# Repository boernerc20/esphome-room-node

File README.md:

# Jarvis Room Node

An ESP32-S3 voice assistant and room sensor for [Home Assistant](https://www.home-assistant.io/),
built on [ESPHome](https://esphome.io/). Wake word ("hey jarvis") on the device, temperature
and humidity, e-ink display, LED status ring.

**Status:** breadboard works end to end. Next: rev A PCB in KiCad.

## Repo

| Path | What |
|---|---|
| [`room-node.yaml`](room-node.yaml) | ESPHome firmware (breadboard pins) |
| [`docs/breadboard.md`](docs/breadboard.md) | Breadboard wiring |
| [`docs/pcb/pinout.md`](docs/pcb/pinout.md) | Rev A PCB pinout |
| [`docs/pcb/schematic.md`](docs/pcb/schematic.md) | Rev A schematic, sheet by sheet — draw from this |
| [`docs/pcb/layout.md`](docs/pcb/layout.md) | Rev A board (placed + routed), assembly and bring-up |
| [`docs/enclosure.md`](docs/enclosure.md) | Enclosure notes |
| `kicad/room-node/` | KiCad project |
| `reports/bom/rev-a-bom-lcsc.csv` | Rev A BOM with LCSC numbers |
| `models/` | Wake word model |

## Flash

1. Copy `secrets.yaml.example` to `secrets.yaml` and fill it in. Git ignores it.
2. `esphome run room-node.yaml` — USB the first time, then OTA (192.168.1.50).
3. Home Assistant finds the node. Assign an Assist pipeline under **Settings → Voice assistants**.

Built by [Chris Boerner](https://boernerc20.me).

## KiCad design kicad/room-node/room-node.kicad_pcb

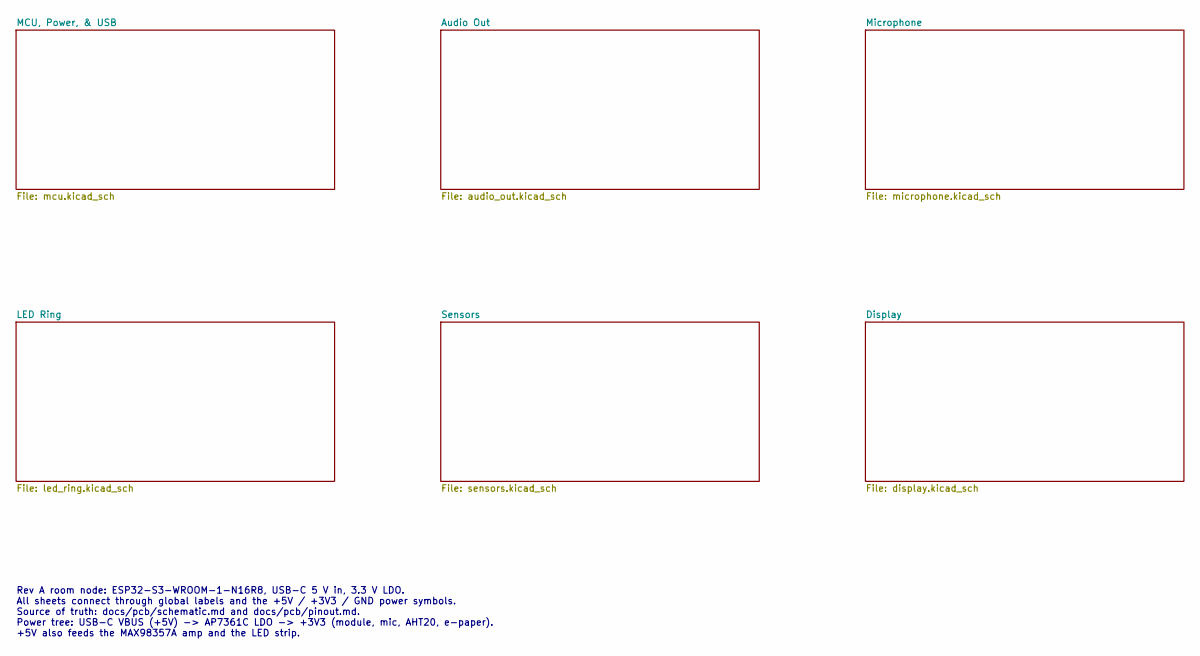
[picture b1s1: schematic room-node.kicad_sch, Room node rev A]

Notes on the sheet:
Rev A room node: ESP32-S3-WROOM-1-N16R8, USB-C 5 V in, 3.3 V LDO. All sheets connect through global labels and the +5V / +3V3 / GND power symbols. Source of truth: docs/pcb/schematic.md and docs/pcb/pinout.md. Power tree: USB-C VBUS (+5V) -> AP7361C LDO -> +3V3 (module, mic, AHT20, e-paper). +5V al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

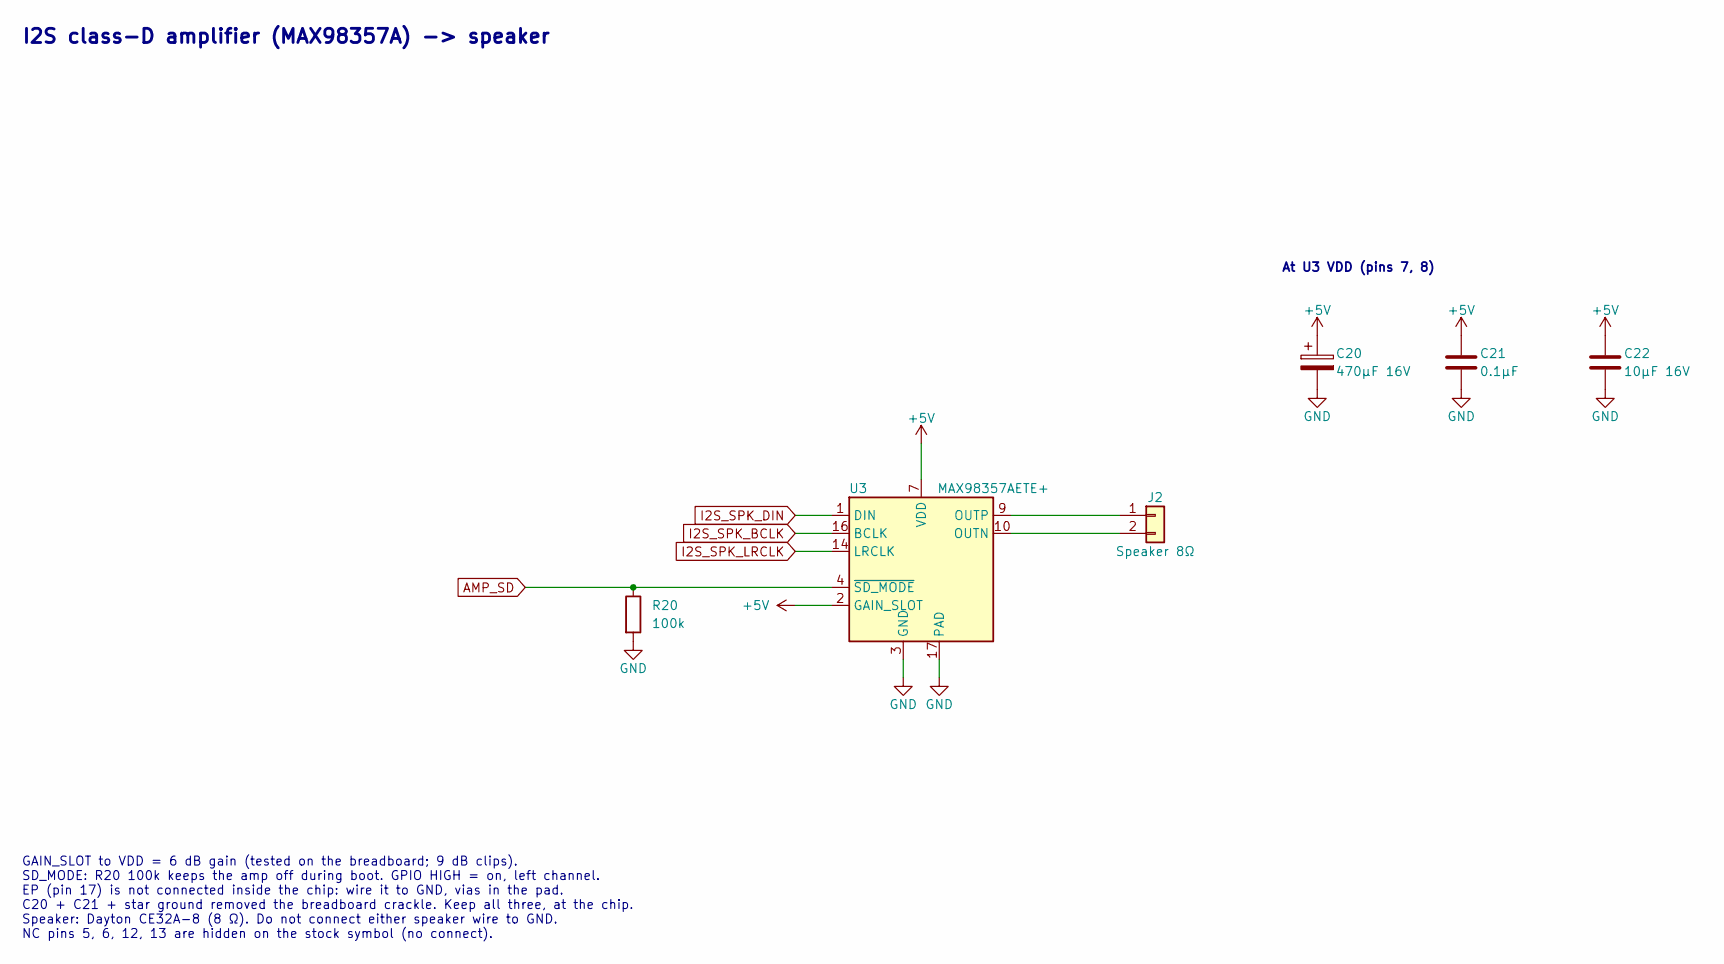
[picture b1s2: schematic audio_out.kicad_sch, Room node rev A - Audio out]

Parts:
C20: 470µF 16V; CP_Radial_D8.0mm_P3.50mm; MPN SamYoung NXB16V470M8*11.5; LCSC C346937
C21: 0.1µF; C_0603_1608Metric; LCSC C14663
C22: 10µF 16V; C_0805_2012Metric; LCSC C15850
J2: Speaker 8Ω; JST_PH_B2B-PH-SM4-TB_1x02-1MP_P2.00mm_Vertical; MPN JST B2B-PH-SM4-TB(LF)(SN); LCSC C160352
R20: 100k; R_0603_1608Metric; LCSC C25803
U3: MAX98357AETE+; TQFN-16-1EP_3x3mm_P0.5mm_EP1.23x1.23mm; MPN Analog Devices MAX98357AETE+; LCSC TBD

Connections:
+5V: C20.1, C21.1, C22.1, U3.2 (GAIN_SLOT), U3.7 (VDD), U3.8 (VDD); also elsewhere on the board
AMP_SD: R20.1, U3.4 (~SD_MODE); also elsewhere on the board
GND: C20.2, C21.2, C22.2, R20.2, U3.3 (GND), U3.11 (GND), U3.15 (GND), U3.17 (PAD); also elsewhere on the board
I2S_SPK_BCLK: U3.16 (BCLK); also elsewhere on the board
I2S_SPK_DIN: U3.1 (DIN); also elsewhere on the board
I2S_SPK_LRCLK: U3.14 (LRCLK); also elsewhere on the board
unnamed: J2.1, U3.9 (OUTP)
unnamed: J2.2, U3.10 (OUTN)

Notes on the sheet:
I2S class-D amplifier (MAX98357A) -> speaker
At U3 VDD (pins 7, 8)
GAIN_SLOT to VDD = 6 dB gain (tested on the breadboard; 9 dB clips). SD_MODE: R20 100k keeps the amp off during boot. GPIO HIGH = on, left channel. EP (pin 17) is not connected inside the chip: wire it to GND, vias in the pad. C20 + C21 + star ground removed the breadboard crackle. Keep all three, 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

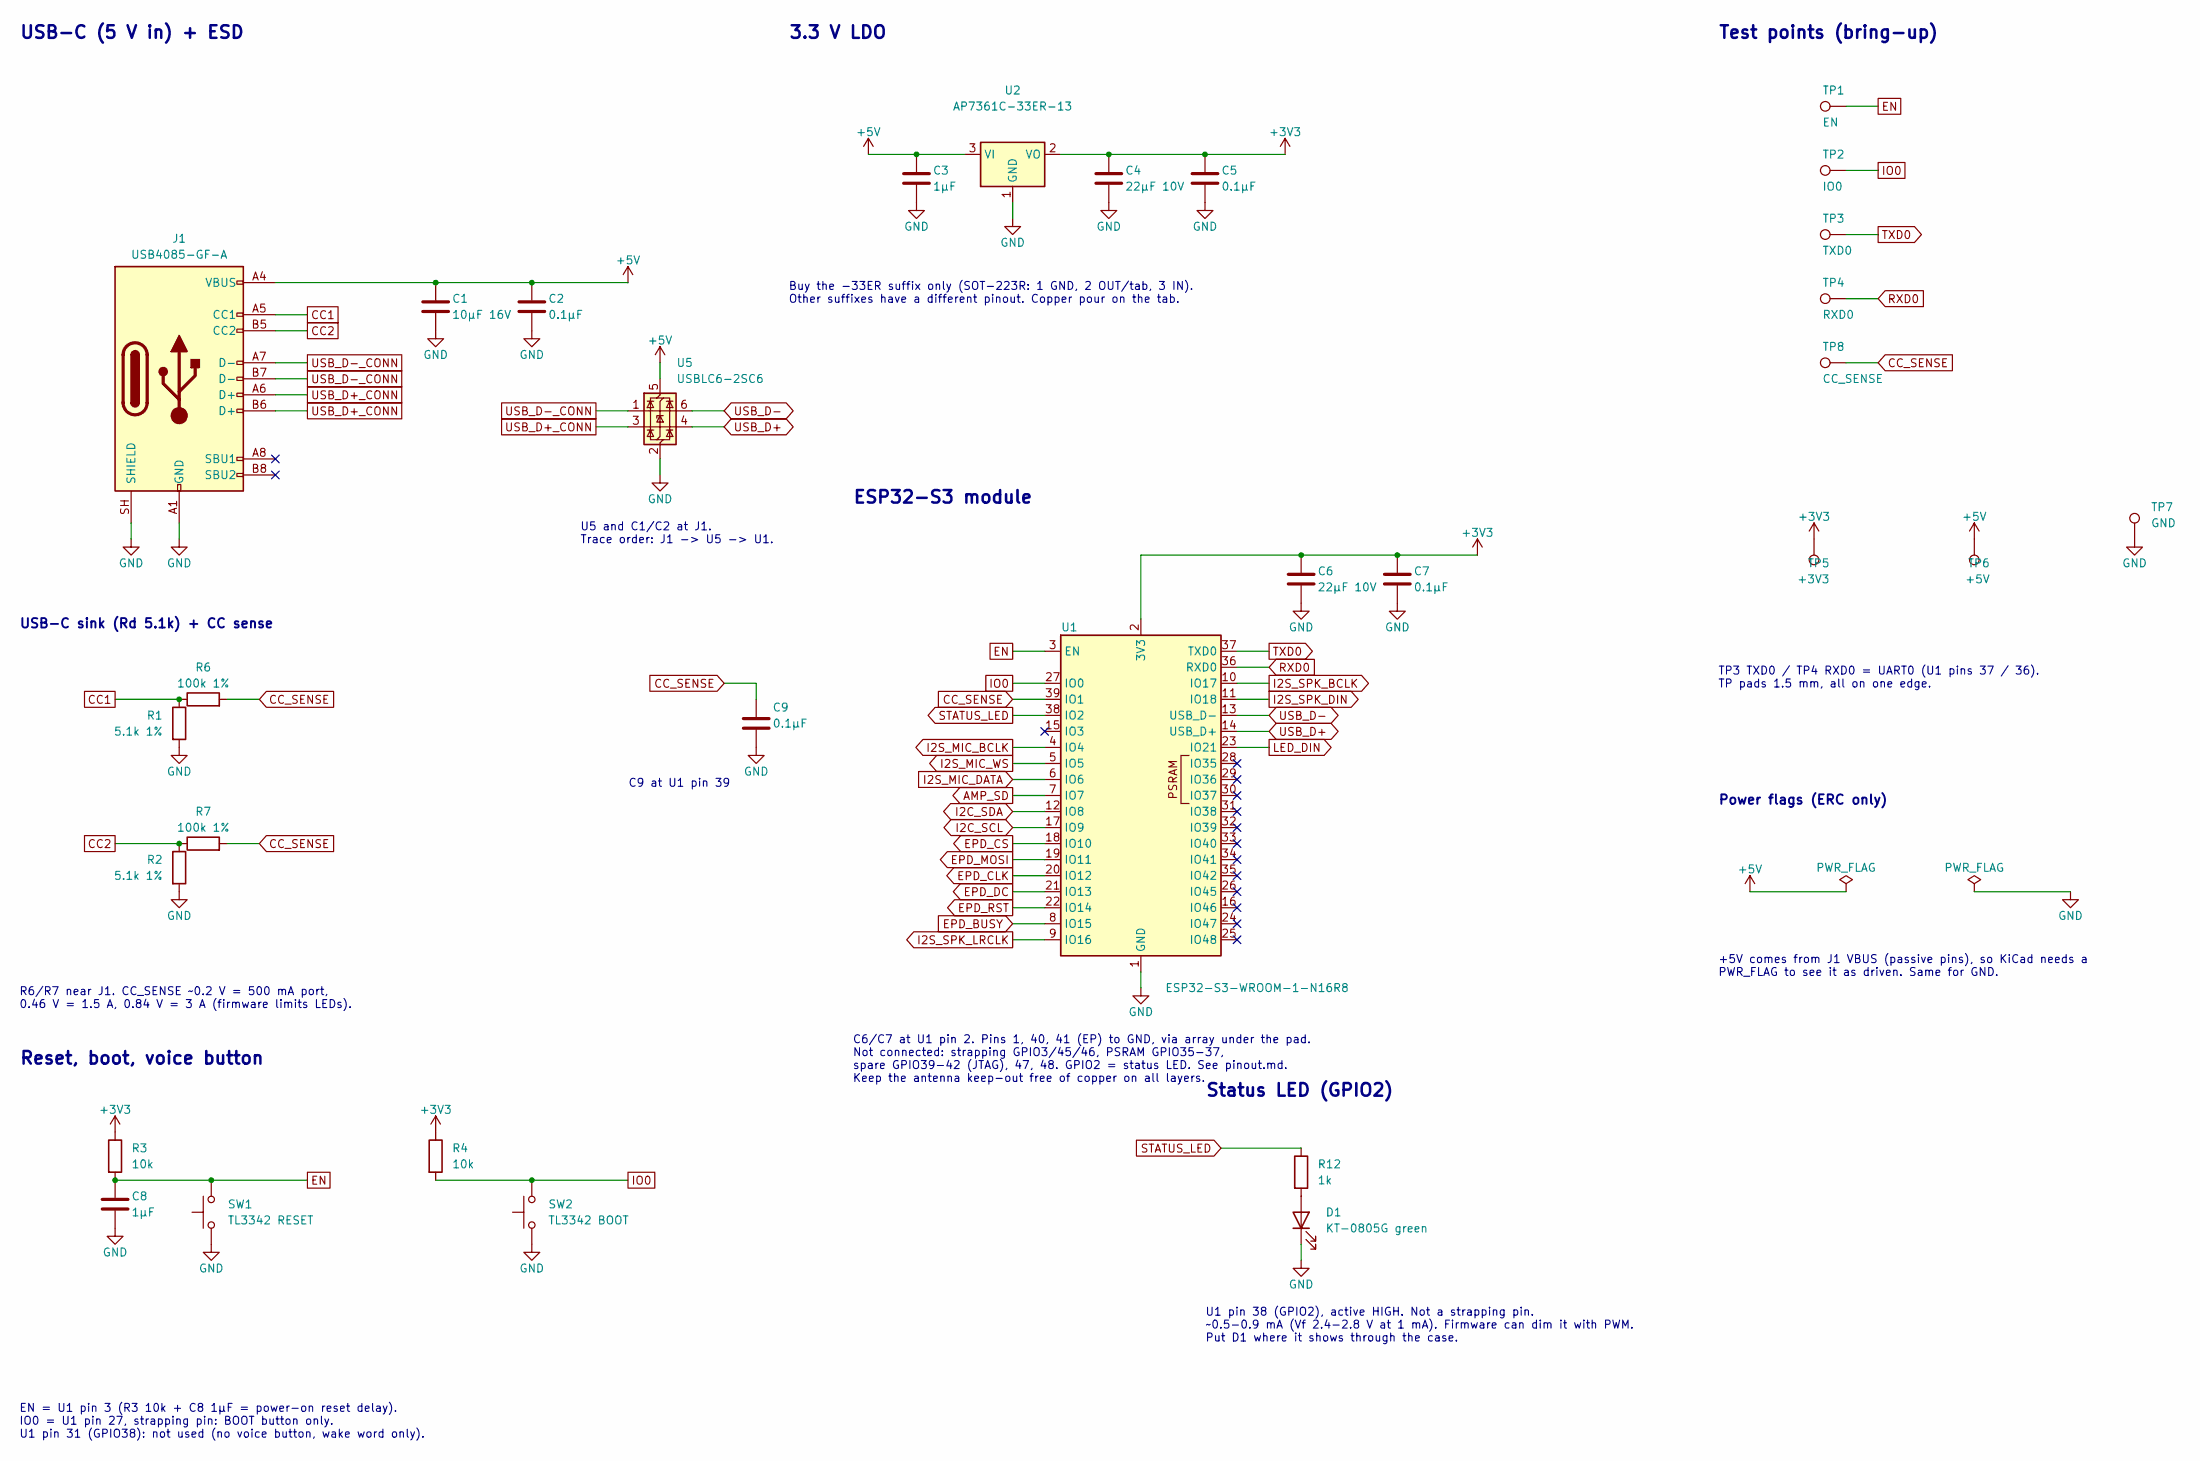
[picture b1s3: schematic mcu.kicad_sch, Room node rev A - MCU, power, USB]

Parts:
C1: 10µF 16V; C_0805_2012Metric; LCSC C15850
C2, C5, C7, C9: 0.1µF; C_0603_1608Metric; LCSC C14663
C3, C8: 1µF; C_0603_1608Metric; LCSC C15849
C4, C6: 22µF 10V; C_0805_2012Metric; LCSC C45783
D1: KT-0805G green; LED_0805_2012Metric; MPN KT-0805G; LCSC C2297
J1: USB4085-GF-A; USB_C_Receptacle_GCT_USB4085; MPN GCT USB4085-GF-A; LCSC TBD
R1, R2: 5.1k 1%; R_0603_1608Metric; LCSC C23186
R3, R4: 10k; R_0603_1608Metric; LCSC C25804
R6, R7: 100k 1%; R_0603_1608Metric; LCSC C25803
R12: 1k; R_0603_1608Metric; LCSC C21190
SW1: TL3342 RESET; SW_SPST_TL3342; MPN E-Switch TL3342F160QG; LCSC TBD
SW2: TL3342 BOOT; SW_SPST_TL3342; MPN E-Switch TL3342F160QG; LCSC TBD
TP1: EN; TestPoint_Pad_D1.5mm
TP2: IO0; TestPoint_Pad_D1.5mm
TP3: TXD0; TestPoint_Pad_D1.5mm
TP4: RXD0; TestPoint_Pad_D1.5mm
TP5: +3V3; TestPoint_Pad_D1.5mm
TP6: +5V; TestPoint_Pad_D1.5mm
TP7: GND; TestPoint_Pad_D1.5mm
TP8: CC_SENSE; TestPoint_Pad_D1.5mm
U1: ESP32-S3-WROOM-1-N16R8; ESP32-S3-WROOM-1; MPN Espressif ESP32-S3-WROOM-1-N16R8; LCSC TBD
U2: AP7361C-33ER-13; SOT-223-3_TabPin2; MPN Diodes AP7361C-33ER-13; LCSC TBD
U5: USBLC6-2SC6; SOT-23-6; MPN ST USBLC6-2SC6; LCSC TBD

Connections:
+3V3: C4.1, C5.1, C6.1, C7.1, R3.1, R4.1, TP5.1, U1.2 (3V3), U2.2 (VO); also elsewhere on the board
+5V: C1.1, C2.1, C3.1, J1.A4 (VBUS), J1.A9 (VBUS), J1.B4 (VBUS), J1.B9 (VBUS), TP6.1, U2.3 (VI), U5.5 (VBUS); also elsewhere on the board
AMP_SD: U1.7 (IO7); also elsewhere on the board
CC1: J1.A5 (CC1), R1.1, R6.1
CC2: J1.B5 (CC2), R2.1, R7.1
CC_SENSE: C9.1, R6.2, R7.2, TP8.1, U1.39 (IO1)
EN: C8.1, R3.2, SW1.2, TP1.1, U1.3 (EN)
EPD_BUSY: U1.8 (IO15); also elsewhere on the board
EPD_CLK: U1.20 (IO12); also elsewhere on the board
EPD_CS: U1.18 (IO10); also elsewhere on the board
EPD_DC: U1.21 (IO13); also elsewhere on the board
EPD_MOSI: U1.19 (IO11); also elsewhere on the board
EPD_RST: U1.22 (IO14); also elsewhere on the board
GND: C1.2, C2.2, C3.2, C4.2, C5.2, C6.2, C7.2, C8.2, C9.2, D1.1 (K), J1.A1 (GND), J1.A12 (GND), J1.B1 (GND), J1.B12 (GND), J1.SH (SHIELD), R1.2, R2.2, SW1.1, SW2.1, TP7.1, U1.1 (GND), U1.40 (GND), U1.41 (GND), U2.1 (GND), U5.2 (GND); also elsewhere on the board
I2C_SCL: U1.17 (IO9); also elsewhere on the board
I2C_SDA: U1.12 (IO8); also elsewhere on the board
I2S_MIC_BCLK: U1.4 (IO4); also elsewhere on the board
I2S_MIC_DATA: U1.6 (IO6); also elsewhere on the board
I2S_MIC_WS: U1.5 (IO5); also elsewhere on the board
I2S_SPK_BCLK: U1.10 (IO17); also elsewhere on the board
I2S_SPK_DIN: U1.11 (IO18); also elsewhere on the board
I2S_SPK_LRCLK: U1.9 (IO16); also elsewhere on the board
IO0: R4.2, SW2.2, TP2.1, U1.27 (IO0)
LED_DIN: U1.23 (IO21); also elsewhere on the board
unnamed: D1.2 (A), R12.2
RXD0: TP4.1, U1.36 (RXD0)
STATUS_LED: R12.1, U1.38 (IO2)
TXD0: TP3.1, U1.37 (TXD0)
USB_D+: U1.14 (USB_D+), U5.4 (I/O2)
USB_D+_CONN: J1.A6 (D+), J1.B6 (D+), U5.3 (I/O2)
USB_D-: U1.13 (USB_D-), U5.6 (I/O1)
USB_D-_CONN: J1.A7 (D-), J1.B7 (D-), U5.1 (I/O1)

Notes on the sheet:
USB-C (5 V in) + ESD
U5 and C1/C2 at J1. Trace order: J1 -> U5 -> U1.
USB-C sink (Rd 5.1k) + CC sense
R6/R7 near J1. CC_SENSE ~0.2 V = 500 mA port, 0.46 V = 1.5 A, 0.84 V = 3 A (firmware limits LEDs).
3.3 V LDO
Buy the -33ER suffix only (SOT-223R: 1 GND, 2 OUT/tab, 3 IN). Other suffixes have a different pinout. Copper pour on the tab.
ESP32-S3 module
C6/C7 at U1 pin 2. Pins 1, 40, 41 (EP) to GND, via array under the pad. Not connected: strapping GPIO3/45/46, PSRAM GPIO35-37, spare GPIO39-42 (JTAG), 47, 48. GPIO2 = status LED. See pinout.md. Keep the antenna keep-out free of copper on all layers.
C9 at U1 pin 39
Reset, boot, voice button
EN = U1 pin 3 (R3 10k + C8 1µF = power-on reset delay). IO0 = U1 pin 27, strapping pin: BOOT button only. U1 pin 31 (GPIO38): not used (no voice button, wake word only).
Test points (bring-up)
TP3 TXD0 / TP4 RXD0 = UART0 (U1 pins 37 / 36). TP pads 1.5 mm, all on one edge.
Power flags (ERC only)
+5V comes from J1 VBUS (passive pins), so KiCad needs a PWR_FLAG to see it as driven. Same for GND.
Status LED (GPIO2)
U1 pin 38 (GPIO2), active HIGH. Not a strapping pin. ~0.5-0.9 mA (Vf 2.4-2.8 V at 1 mA). Firmware can dim it with PWM. Put D1 where it shows through the case.

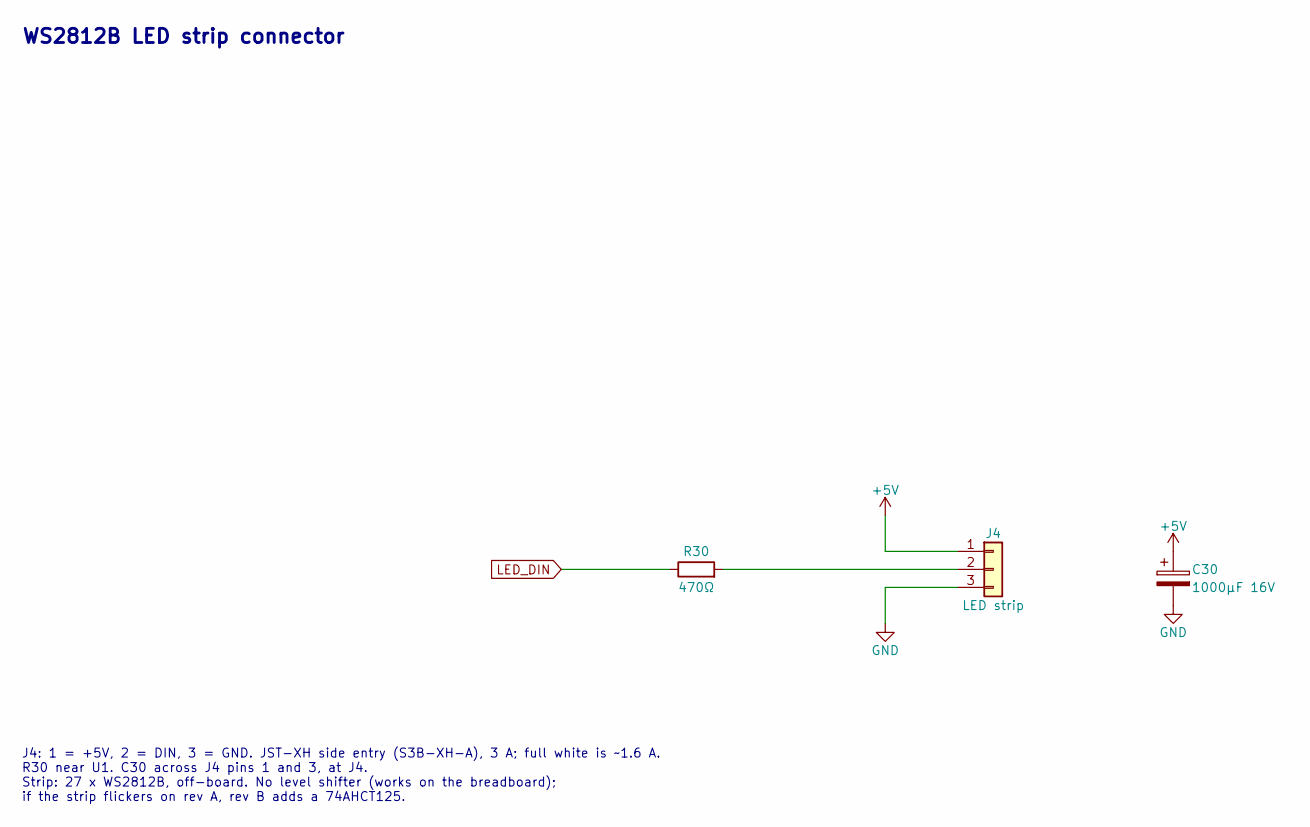
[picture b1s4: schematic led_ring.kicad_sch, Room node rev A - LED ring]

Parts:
C30: 1000µF 16V; CP_Radial_D10.0mm_P5.00mm; MPN SamYoung NHA16V1000M10*16; LCSC C2835709
J4: LED strip; JST_XH_S3B-XH-A_1x03_P2.50mm_Horizontal; MPN JST S3B-XH-A(LF)(SN); LCSC C157928
R30: 470Ω; R_0603_1608Metric; LCSC C23179

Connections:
+5V: C30.1, J4.1; also elsewhere on the board
GND: C30.2, J4.3; also elsewhere on the board
LED_DIN: R30.1; also elsewhere on the board
unnamed: J4.2, R30.2

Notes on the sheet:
WS2812B LED strip connector
J4: 1 = +5V, 2 = DIN, 3 = GND. JST-XH side entry (S3B-XH-A), 3 A; full white is ~1.6 A. R30 near U1. C30 across J4 pins 1 and 3, at J4. Strip: 27 x WS2812B, off-board. No level shifter (works on the breadboard); if the strip flickers on rev A, rev B adds a 74AHCT125.

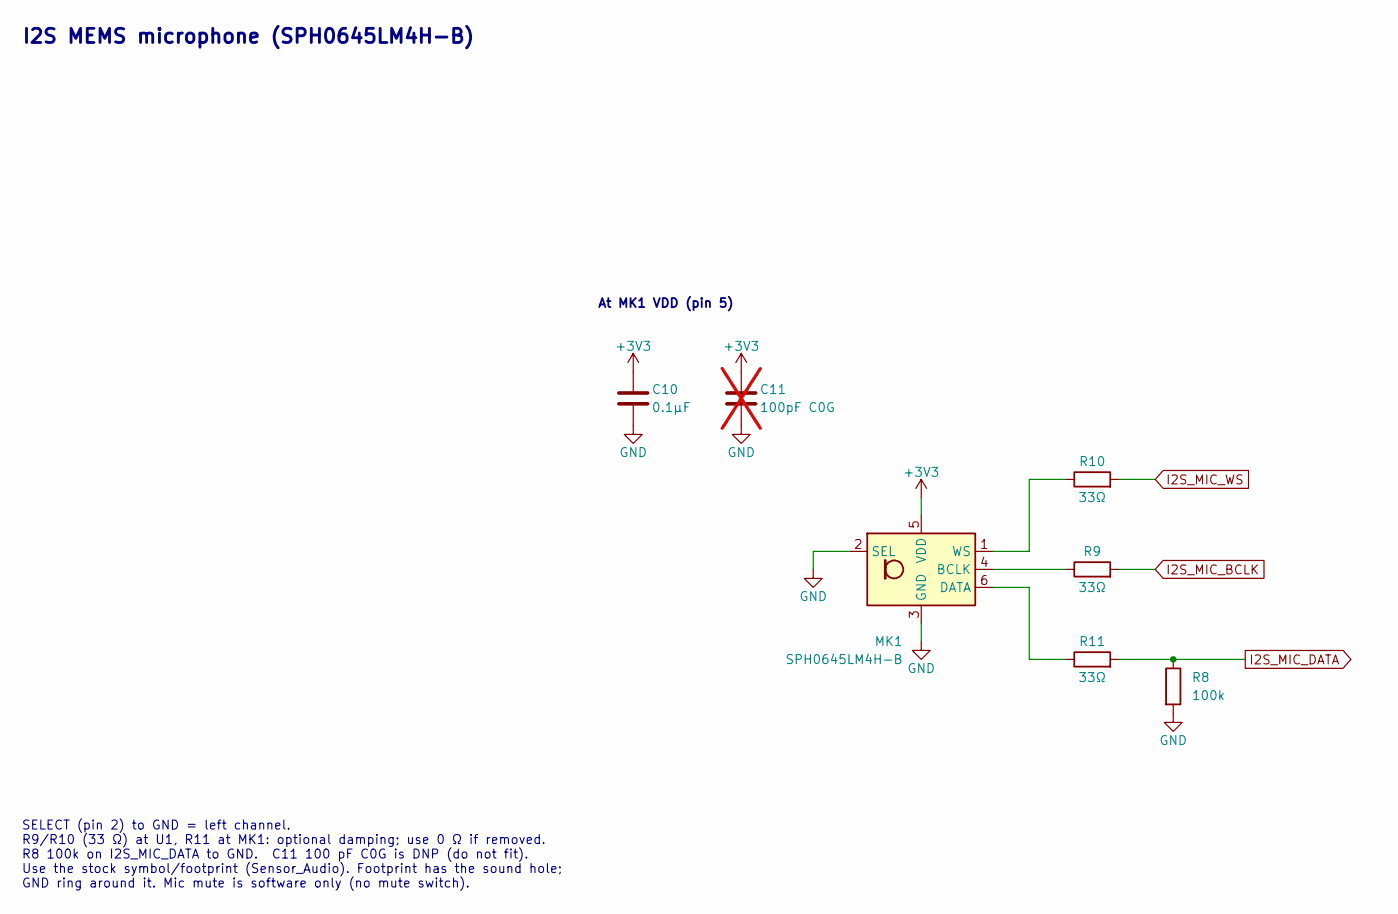
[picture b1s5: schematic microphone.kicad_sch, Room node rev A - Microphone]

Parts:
C10: 0.1µF; C_0603_1608Metric; LCSC C14663
C11: 100pF C0G; C_0603_1608Metric; LCSC C14858; not fitted
MK1: SPH0645LM4H-B; Knowles_SPH0645LM4H-6_3.5x2.65mm; MPN Knowles/Syntiant SPH0645LM4H-B; LCSC TBD
R8: 100k; R_0603_1608Metric; LCSC C25803
R9, R10, R11: 33Ω; R_0603_1608Metric; MPN Uniroyal 0603WAF330JT5E; LCSC C23140

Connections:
+3V3: C10.1, C11.1, MK1.5 (VDD); also elsewhere on the board
GND: C10.2, C11.2, MK1.2 (SEL), MK1.3 (GND), R8.2; also elsewhere on the board
I2S_MIC_BCLK: R9.2; also elsewhere on the board
I2S_MIC_DATA: R8.1, R11.2; also elsewhere on the board
I2S_MIC_WS: R10.2; also elsewhere on the board
unnamed: MK1.4 (BCLK), R9.1
unnamed: MK1.6 (DATA), R11.1
unnamed: MK1.1 (WS), R10.1

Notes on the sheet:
I2S MEMS microphone (SPH0645LM4H-B)
At MK1 VDD (pin 5)
SELECT (pin 2) to GND = left channel. R9/R10 (33 Ω) at U1, R11 at MK1: optional damping; use 0 Ω if removed. R8 100k on I2S_MIC_DATA to GND. C11 100 pF C0G is DNP (do not fit). Use the stock symbol/footprint (Sensor_Audio). Footprint has the sound hole; GND ring around it. Mic mute is software only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

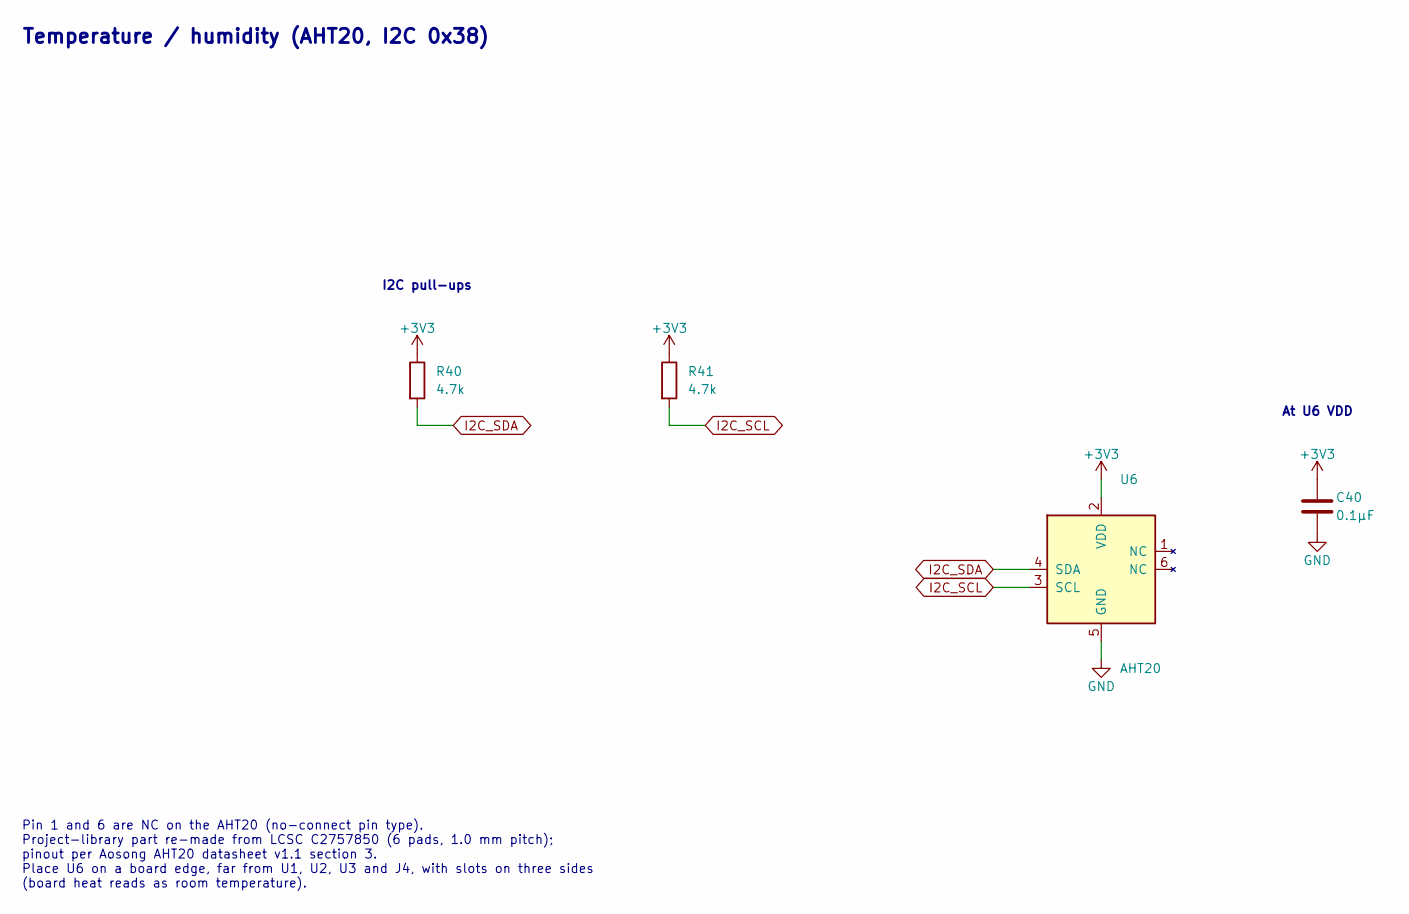
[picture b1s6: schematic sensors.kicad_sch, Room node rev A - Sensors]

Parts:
C40: 0.1µF; C_0603_1608Metric; LCSC C14663
R40, R41: 4.7k; R_0603_1608Metric; LCSC C23162
U6: AHT20; MPN Aosong AHT20; LCSC C2757850

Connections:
+3V3: C40.1, R40.1, R41.1, U6.2 (VDD); also elsewhere on the board
GND: C40.2, U6.5 (GND); also elsewhere on the board
I2C_SCL: R41.2, U6.3 (SCL); also elsewhere on the board
I2C_SDA: R40.2, U6.4 (SDA); also elsewhere on the board

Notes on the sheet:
Temperature / humidity (AHT20, I2C 0x38)
At U6 VDD
I2C pull-ups
Pin 1 and 6 are NC on the AHT20 (no-connect pin type). Project-library part re-made from LCSC C2757850 (6 pads, 1.0 mm pitch); pinout per Aosong AHT20 datasheet v1.1 section 3. Place U6 on a board edge, far from U1, U2, U3 and J4, with slots on three sides (board heat reads as room temperature).

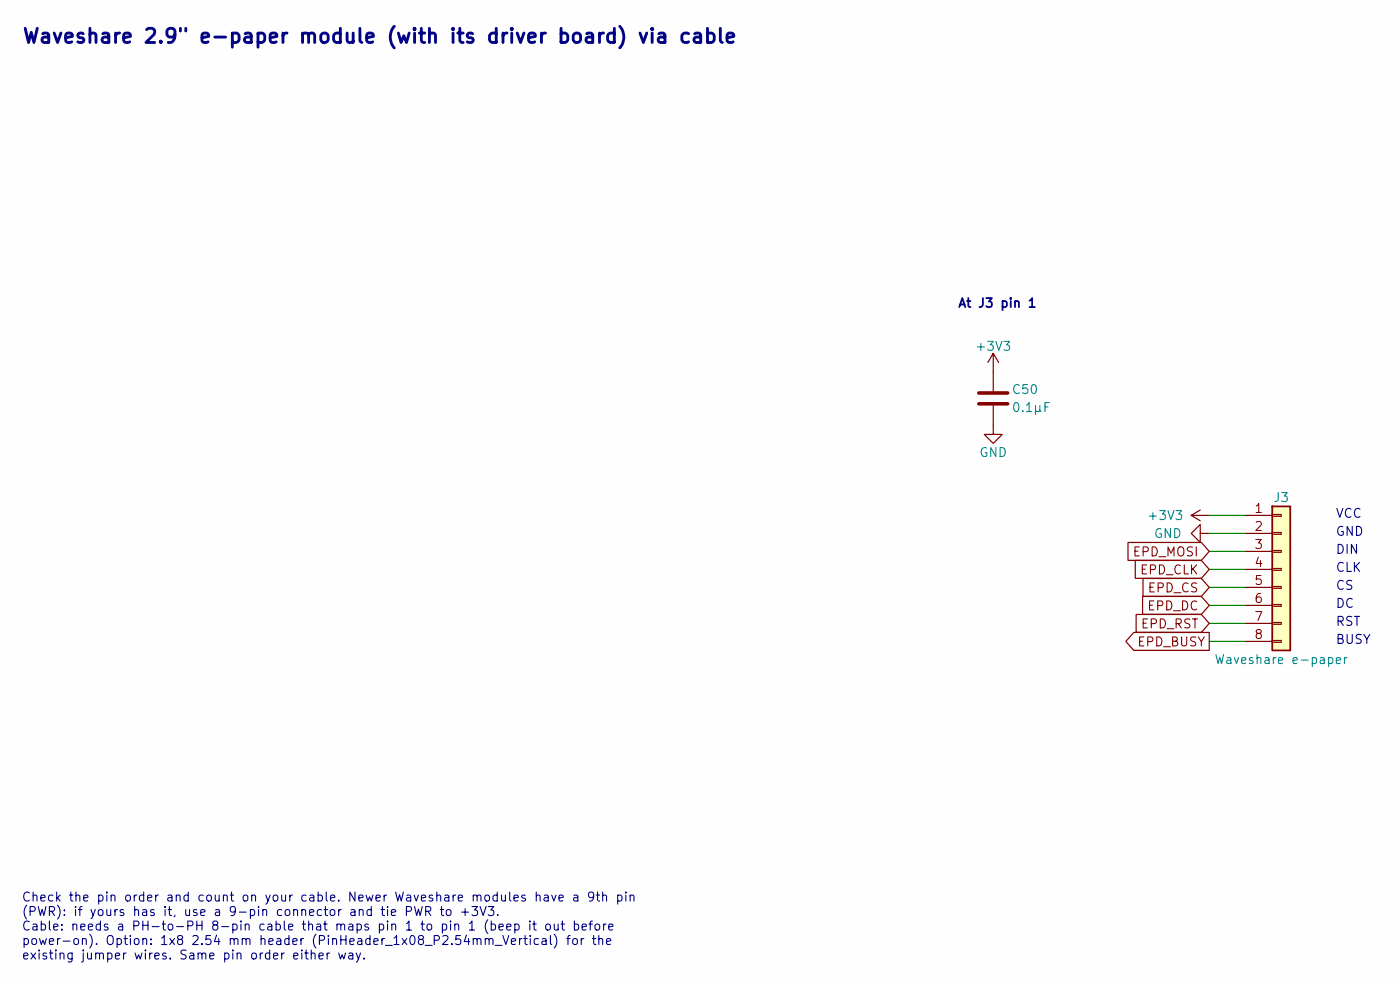
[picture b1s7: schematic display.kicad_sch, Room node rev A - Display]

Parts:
C50: 0.1µF; C_0603_1608Metric; LCSC C14663
J3: Waveshare e-paper; JST_PH_S8B-PH-SM4-TB_1x08-1MP_P2.00mm_Horizontal; MPN JST S8B-PH-SM4-TB(LF)(SN); LCSC C265121

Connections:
+3V3: C50.1, J3.1; also elsewhere on the board
EPD_BUSY: J3.8; also elsewhere on the board
EPD_CLK: J3.4; also elsewhere on the board
EPD_CS: J3.5; also elsewhere on the board
EPD_DC: J3.6; also elsewhere on the board
EPD_MOSI: J3.3; also elsewhere on the board
EPD_RST: J3.7; also elsewhere on the board
GND: C50.2, J3.2; also elsewhere on the board

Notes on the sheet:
Waveshare 2.9" e-paper module (with its driver board) via cable
VCC
GND
DIN
CLK
RST
BUSY
At J3 pin 1
Check the pin order and count on your cable. Newer Waveshare modules have a 9th pin (PWR): if yours has it, use a 9-pin connector and tie PWR to +3V3. Cable: needs a PH-to-PH 8-pin cable that maps pin 1 to pin 1 (beep it out before power-on). Option: 1x8 2.54 mm header (PinHeader_1x08_P2.54mm_Verti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

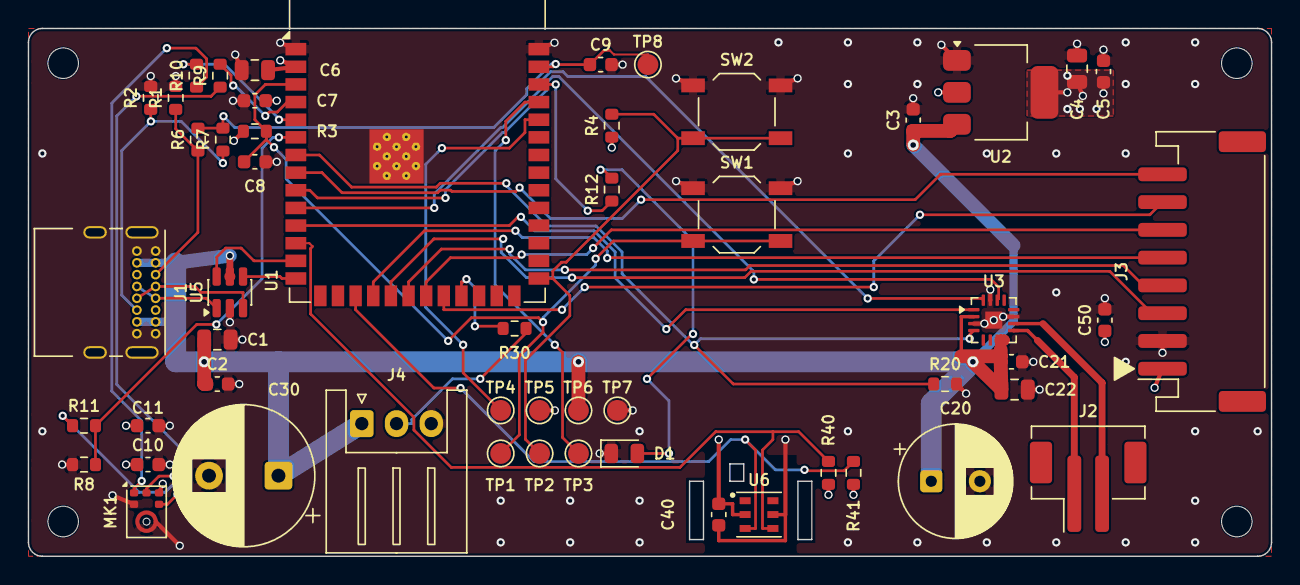
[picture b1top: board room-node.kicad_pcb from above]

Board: 4 copper layers, 89.5 x 38.0 mm, 57 parts (0 on the bottom side), 38 nets.

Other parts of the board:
H1, H2, H3, H4: M2; MountingHole_2.2mm_M2

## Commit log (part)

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2026-05-07 Initial commit: ESPHome room node with AHT20 sensor and e-ink display
